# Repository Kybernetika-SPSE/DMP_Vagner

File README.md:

# Smart Hive

**Smart Hive** je projekt zaměřený na monitorování včelích úlů pomocí senzorů, které sbírají důležitá data o prostředí v úlech a jejich okolí. Data jsou přenášena přes I2C sběrnici do centrální (master) jednotky, která je dále odesílá do databáze. K těmto datům mohou uživatelé přistupovat online prostřednictvím webového rozhraní.

## Funkce
- **Sběr dat**: Senzory instalované ve včelích úlech monitorují teplotu, vlhkost, hmotnost úlu a hlukové znečištění.
- **Přenos dat**: Data z jednotlivých úlů jsou sbírána pomocí I2C komunikace a odesílána do centrální jednotky.
- **Uložení dat**: Centrální jednotka data ukládá do databáze.
- **Přístup k datům**: Uživatelé mohou přistupovat k datům online prostřednictvím webového rozhraní.

## Technické detaily
- **I2C komunikace**: Využívá se pro přenos dat mezi senzory v úlech a centrální jednotkou.
- **Databáze**: Data jsou ukládána do vzdálené databáze, která je přístupná uživatelům online.
- **Centrální jednotka**: Hlavní jednotka přijímá data od senzorů a zajišťuje jejich odesílání do databáze.
- **Webové rozhraní**: Poskytuje uživatelům přístup k živým datům a historickým záznamům.

## Požadavky
- **Hardware**: ESP32 s podporou I2C, senzory pro měření teploty, vlhkosti, hmotnosti a hluku, včelí úly.
- **Software**: Podpora I2C komunikace, databázový systém (např. MySQL, PostgreSQL), webový server pro přístup k datům.

## Použití
Po úspěšné instalaci systém začne shromažďovat a odesílat data ze senzorů v reálném čase. Uživatelé mohou k těmto datům přistupovat pomocí webového rozhraní, které umožňuje sledovat aktuální stav úlů a analyzovat historická data.

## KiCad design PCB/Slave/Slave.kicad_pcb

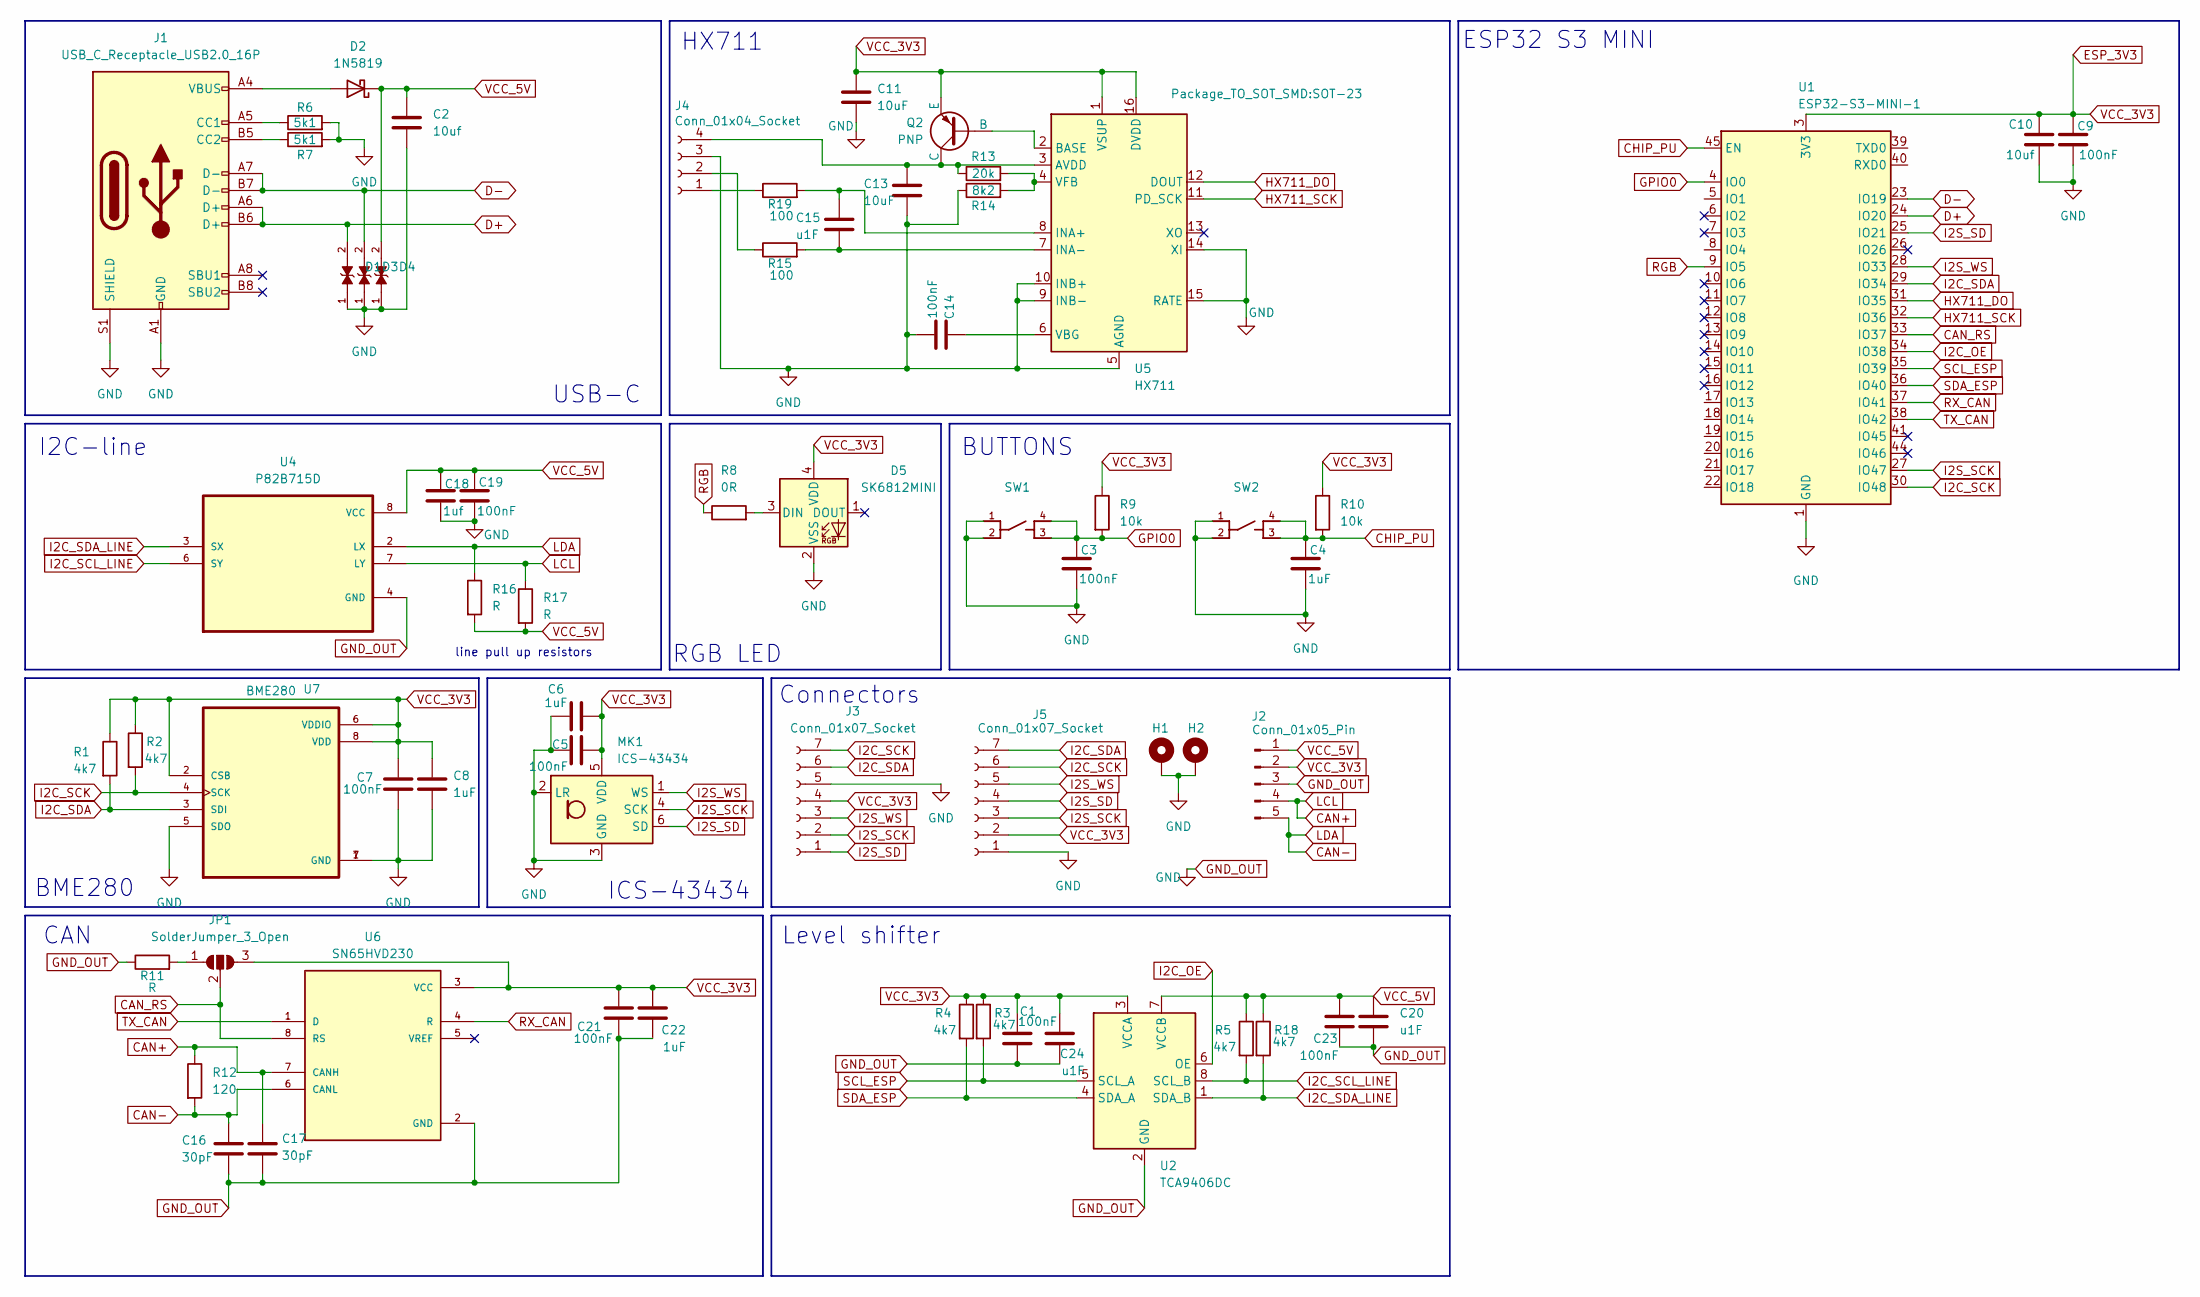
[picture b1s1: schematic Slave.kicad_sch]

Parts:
C1, C3, C5, C7, C9, C14, C19, C21, C23: 100nF; C_0603_1608Metric_Pad1.08x0.95mm_HandSolder
C2, C10: 10uf; C_0603_1608Metric_Pad1.08x0.95mm_HandSolder
C4, C6, C8, C22: 1uF; C_0603_1608Metric_Pad1.08x0.95mm_HandSolder
C11, C13: 10uF; C_0603_1608Metric_Pad1.08x0.95mm_HandSolder
C15, C20, C24: u1F; C_0603_1608Metric_Pad1.08x0.95mm_HandSolder
C16, C17: 30pF; C_0603_1608Metric_Pad1.08x0.95mm_HandSolder
C18: 1uf; C_0603_1608Metric_Pad1.08x0.95mm_HandSolder
D1, D3, D4: LESD5D5.0CT1G; TVS_LESD5D5.0CT1G; PARTREV O
D2: 1N5819; Nexperia_CFP3_SOD-123W
D5: SK6812MINI; LED_SK6812MINI_PLCC4_3.5x3.5mm_P1.75mm
H1, H2: MountingHole_Pad_MP; MountingHole_2.2mm_M2_Pad_Via
J1: USB_C_Receptacle_USB2.0_16P; USB_C_Receptacle_GCT_USB4105-xx-A_16P_TopMnt_Horizontal
J2: Conn_01x05_Pin; TerminalBlock_Phoenix_MPT-0,5-5-2.54_1x05_P2.54mm_Horizontal
J3: Conn_01x07_Socket; PinSocket_1x07_P2.54mm_Vertical
J4: Conn_01x04_Socket; PinHeader_1x04_P2.54mm_Vertical
J5: Conn_01x07_Socket; PinHeader_1x07_P1.00mm_Vertical_SMD_Pin1Left
JP1: SolderJumper_3_Open; SolderJumper-3_P1.3mm_Open_RoundedPad1.0x1.5mm
MK1: ICS-43434; InvenSense_ICS-43434-6_3.5x2.65mm
Q2: PNP; SOT-23
R1, R2, R3, R4, R5, R18: 4k7; R_0603_1608Metric_Pad0.98x0.95mm_HandSolder
R6, R7: 5k1; R_0603_1608Metric_Pad0.98x0.95mm_HandSolder
R8: 0R; R_0603_1608Metric_Pad0.98x0.95mm_HandSolder
R9, R10: 10k; R_0603_1608Metric_Pad0.98x0.95mm_HandSolder
R11, R16, R17: R; R_0603_1608Metric_Pad0.98x0.95mm_HandSolder
R12: 120; R_0603_1608Metric_Pad0.98x0.95mm_HandSolder
R13: 20k; R_0603_1608Metric_Pad0.98x0.95mm_HandSolder
R14: 8k2; R_0603_1608Metric_Pad0.98x0.95mm_HandSolder
R15, R19: 100; R_0603_1608Metric_Pad0.98x0.95mm_HandSolder
SW1, SW2: PTS810_SJM_250_SMTR_LFS; SW_PTS810_SJM_250_SMTR_LFS
U1: ESP32-S3-MINI-1; XCVR_ESP32-S3-MINI-1-N8
U2: TCA9406DC; SOP50P310X90-8N
U4: P82B715D; SOIC127P599X175-8N
U5: HX711; SOP-16_3.9x9.9mm_P1.27mm
U6: SN65HVD230; SOIC127P599X175-8N; PARTREV 02/2019
U7: BME280; PSON65P250X250X100-8N

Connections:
CAN+: C17.1, J2.4, R12.1, R17.1, U4.7 (LY), U6.7 (CANH)
CAN-: C16.1, J2.5, R12.2, R16.1, U4.2 (LX), U6.6 (CANL)
CAN_RS: JP1.2 (C), U1.33 (IO37), U6.8 (RS)
CHIP_PU: C4.1, R10.2, SW2.3, SW2.4, U1.45 (EN)
D+: D1.2, J1.A6 (D+), J1.B6 (D+), U1.24 (IO20)
D-: D3.2, J1.A7 (D-), J1.B7 (D-), U1.23 (IO19)
ESP_3V3: C1.2, C5.2, C6.2, C7.1, C8.1, C9.1, C10.1, C11.1, C21.1, C22.1, C24.1, D5.4 (VDD), J2.2, J3.4, J5.2, JP1.3 (B), MK1.5 (VDD), Q2.3 (E), R1.1, R2.1, R3.1, R4.1, R9.1, R10.1, U1.3 (3V3), U2.3 (VCCA), U5.1 (VSUP), U5.16 (DVDD), U6.3 (VCC), U7.2 (CSB), U7.6 (VDDIO), U7.8 (VDD)
GND_OUT: C1.1, C2.2, C3.2, C4.2, C5.1, C6.1, C7.2, C8.2, C9.2, C10.2, C11.2, C13.2, C14.2, C16.2, C17.2, C18.2, C19.2, C20.2, C21.2, C22.2, C23.1, C24.2, D1.1, D3.1, D4.1, D5.2 (VSS), H1.1, H2.1, J1.A1 (GND), J1.A12 (GND), J1.B1 (GND), J1.B12 (GND), J1.S1 (SHIELD), J2.3, J3.5, J4.3, J5.1, MK1.2 (LR), MK1.3 (GND), R6.2, R7.2, R11.1, R14.1, SW1.1, SW1.2, SW2.1, SW2.2, U1.1 (GND), U1.2 (GND), U1.42 (GND), U1.43 (GND), U1.46 (GND), U1.47 (GND), U1.48 (GND), U1.49 (GND), U1.50 (GND), U1.51 (GND), U1.52 (GND), U1.53 (GND), U1.54 (GND), U1.55 (GND), U1.56 (GND), U1.57 (GND), U1.58 (GND), U1.59 (GND), U1.60 (GND), U1.61 (GND), U1.62 (GND), U1.63 (GND), U1.64 (GND), U1.65 (GND), U2.2 (GND), U4.4 (GND), U5.5 (AGND), U5.9 (INB-), U5.10 (INB+), U5.14 (XI), U5.15 (RATE), U6.2 (GND), U7.1 (GND), U7.5 (SDO), U7.7 (GND)
GPIO0: C3.1, R9.2, SW1.3, SW1.4, U1.4 (IO0)
HX711_DO: U1.31 (IO35), U5.12 (DOUT)
HX711_SCK: U1.32 (IO36), U5.11 (PD_SCK)
I2C_OE: U1.34 (IO38), U2.6 (OE)
I2C_SCK: J3.7, J5.6, R2.2, U1.30 (IO48), U7.4 (SCK)
I2C_SCL_LINE: R5.2, U2.8 (SCL_B), U4.6 (SY)
I2C_SDA: J3.6, J5.7, R1.2, U1.29 (IO34), U7.3 (SDI)
I2C_SDA_LINE: R18.2, U2.1 (SDA_B), U4.3 (SX)
I2S_SCK: J3.2, J5.3, MK1.4 (SCK), U1.27 (IO47)
I2S_SD: J3.1, J5.4, MK1.6 (SD), U1.25 (IO21)
I2S_WS: J3.3, J5.5, MK1.1 (WS), U1.28 (IO33)
unnamed: D2.2 (A), J1.A4 (VBUS), J1.A9 (VBUS), J1.B4 (VBUS), J1.B9 (VBUS)
unnamed: D5.3 (DIN), R8.2
unnamed: J1.A5 (CC1), R6.1
unnamed: J1.B5 (CC2), R7.1
unnamed: J4.1, R19.1
unnamed: J4.2, R15.1
unnamed: C13.1, J4.4, Q2.1 (C), R13.1, U5.3 (AVDD)
unnamed: JP1.1 (A), R11.2
unnamed: Q2.2 (B), U5.2 (BASE)
unnamed: C15.1, R19.2, U5.8 (INA+)
unnamed: C15.2, R15.2, U5.7 (INA-)
unnamed: C14.1, U5.6 (VBG)
unnamed: R13.2, R14.2, U5.4 (VFB)
RGB: R8.1, U1.9 (IO5)
RX_CAN: U1.37 (IO41), U6.4 (R)
SCL_ESP: R3.2, U1.35 (IO39), U2.5 (SCL_A)
SDA_ESP: R4.2, U1.36 (IO40), U2.4 (SDA_A)
TX_CAN: U1.38 (IO42), U6.1 (D)
VCC_5V: C2.1, C18.1, C19.1, C20.1, C23.2, D2.1 (K), D4.2, J2.1, R5.1, R16.2, R17.2, R18.1, U2.7 (VCCB), U4.8 (VCC)

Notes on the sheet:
RGB LED
Connectors
BUTTONS
I2C-line
line pull up resistors
HX711
CAN
ICS-43434
Level shifter
BME280
ESP32 S3 MINI
USB-C

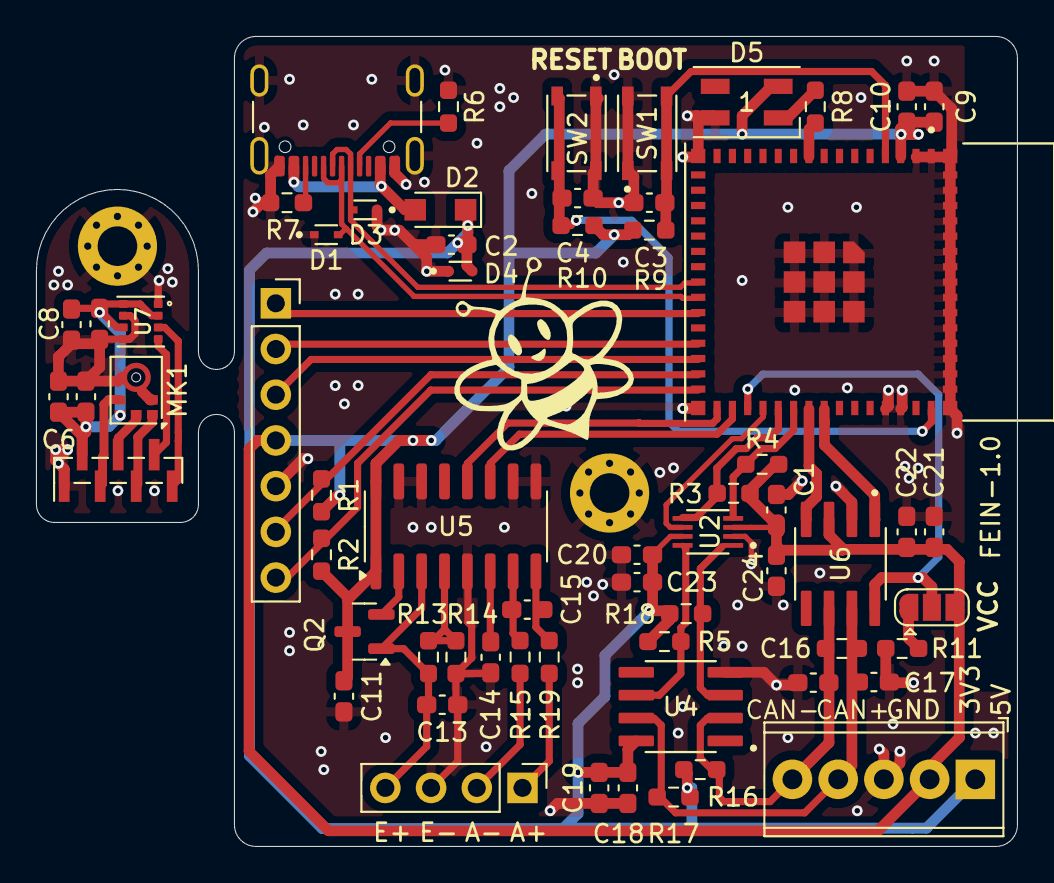
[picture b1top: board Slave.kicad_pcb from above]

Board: 2 copper layers, 54.5 x 45.0 mm, 65 parts (0 on the bottom side), 38 nets.

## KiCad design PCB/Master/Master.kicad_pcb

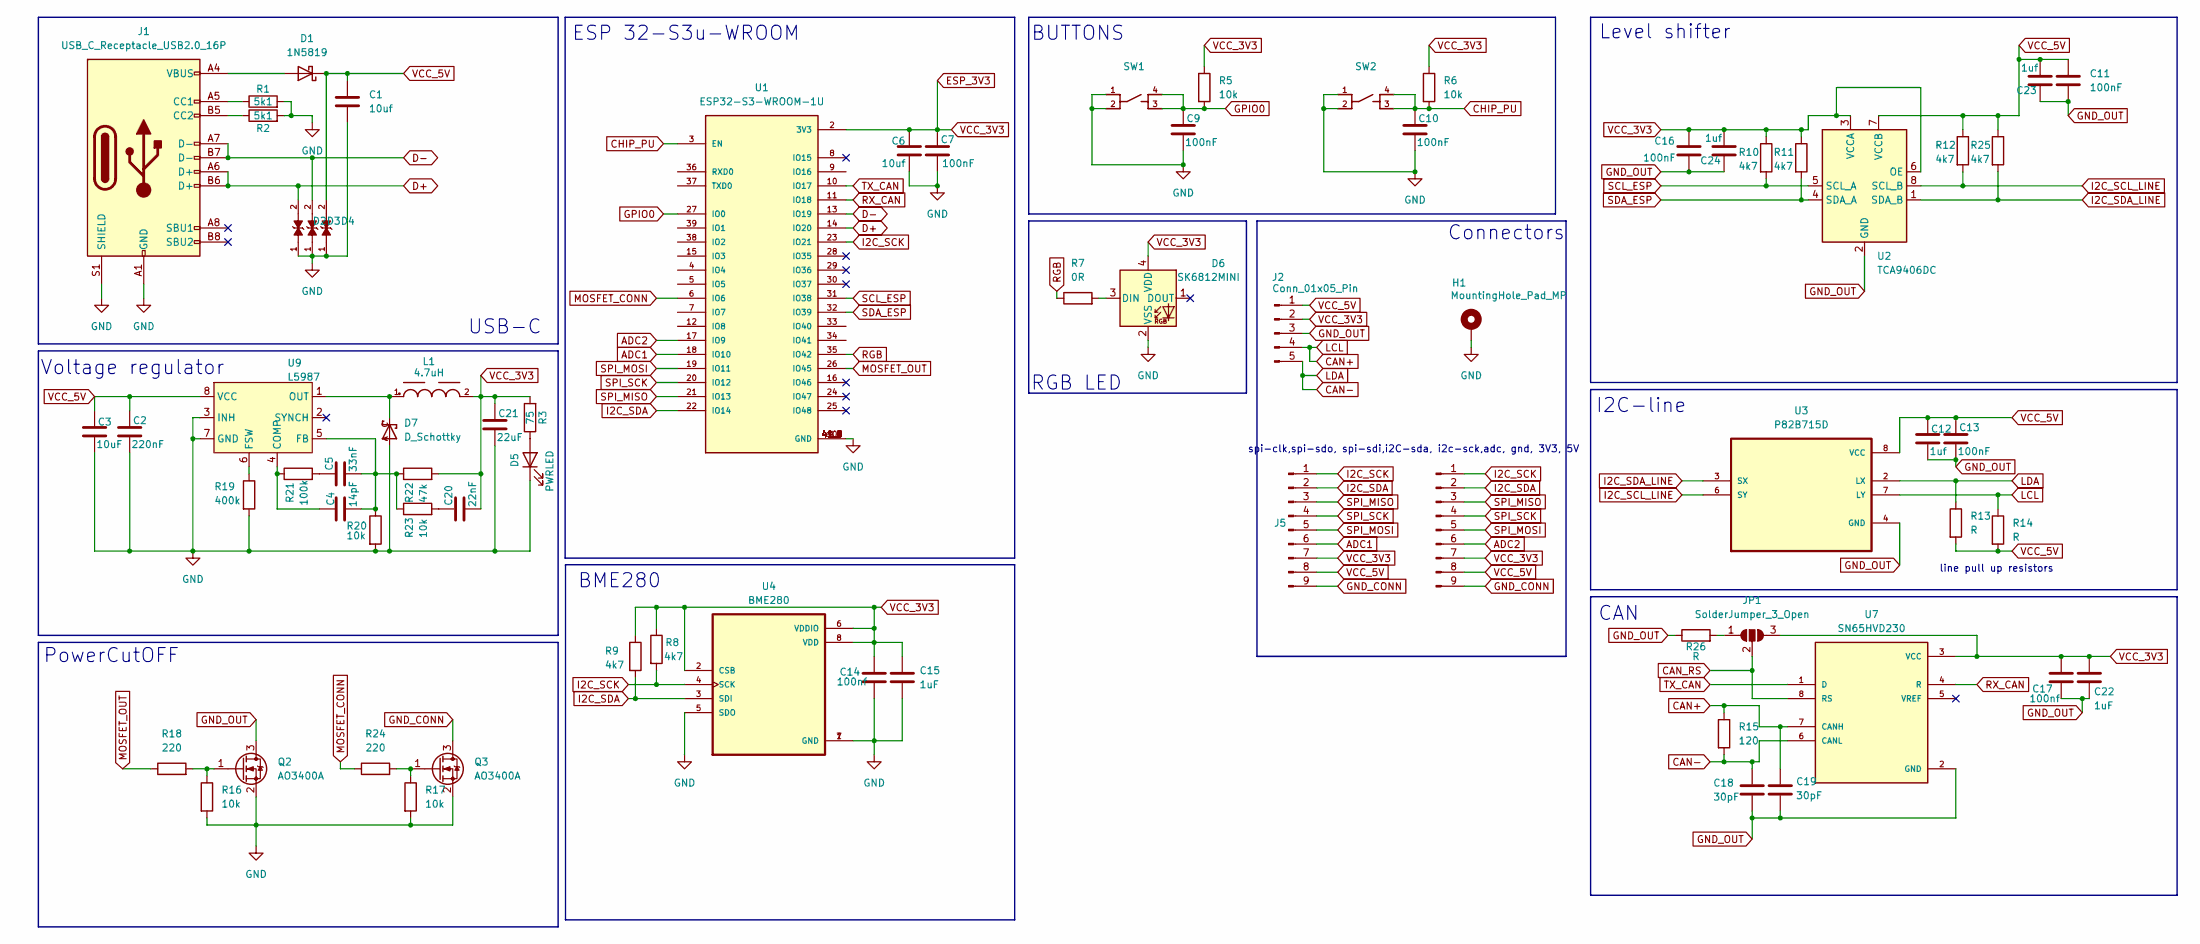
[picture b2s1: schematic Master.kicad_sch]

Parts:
C1, C6: 10uf; C_0603_1608Metric_Pad1.08x0.95mm_HandSolder
C2: 220nF; C_0603_1608Metric_Pad1.08x0.95mm_HandSolder
C3: 10uF; C_0603_1608Metric_Pad1.08x0.95mm_HandSolder
C4: 14pF; C_0603_1608Metric_Pad1.08x0.95mm_HandSolder
C5: 33nF; C_0603_1608Metric_Pad1.08x0.95mm_HandSolder
C7, C9, C10, C11, C13, C16: 100nF; C_0603_1608Metric_Pad1.08x0.95mm_HandSolder
C12, C23, C24: 1uf; C_0603_1608Metric_Pad1.08x0.95mm_HandSolder
C14, C17: 100nf; C_0603_1608Metric_Pad1.08x0.95mm_HandSolder
C15, C22: 1uF; C_0603_1608Metric_Pad1.08x0.95mm_HandSolder
C18, C19: 30pF; C_0603_1608Metric_Pad1.08x0.95mm_HandSolder
C20: 22nF; C_0603_1608Metric_Pad1.08x0.95mm_HandSolder
C21: 22uF; C_0603_1608Metric_Pad1.08x0.95mm_HandSolder
D1: 1N5819; Nexperia_CFP3_SOD-123W
D2, D3, D4: LESD5D5.0CT1G; TVS_LESD5D5.0CT1G; PARTREV O
D5: PWRLED; LED_0603_1608Metric_Pad1.05x0.95mm_HandSolder
D6: SK6812MINI; LED_SK6812MINI_PLCC4_3.5x3.5mm_P1.75mm
D7: D_Schottky; SOD-123
H1: MountingHole_Pad_MP; MountingHole_2.2mm_M2_Pad_Via
J1: USB_C_Receptacle_USB2.0_16P; USB_C_Receptacle_GCT_USB4105-xx-A_16P_TopMnt_Horizontal
J2: Conn_01x05_Pin; TerminalBlock_Phoenix_MPT-0,5-5-2.54_1x05_P2.54mm_Horizontal
J5, J6: Conn_01x09_Pin; PinHeader_1x09_P2.54mm_Vertical
JP1: SolderJumper_3_Open; SolderJumper-3_P1.3mm_Open_RoundedPad1.0x1.5mm
L1: 4.7uH; WE-PD2_5848; DigiKey_Part_Number 732-1272-2-ND
Q2, Q3: AO3400A; SOT-23
R1, R2: 5k1; R_0603_1608Metric_Pad0.98x0.95mm_HandSolder
R3: 75; R_0603_1608Metric_Pad0.98x0.95mm_HandSolder
R5, R6, R16, R17, R20, R23: 10k; R_0603_1608Metric_Pad0.98x0.95mm_HandSolder
R7: 0R; R_0603_1608Metric_Pad0.98x0.95mm_HandSolder
R8, R9, R10, R11, R12, R25: 4k7; R_0603_1608Metric_Pad0.98x0.95mm_HandSolder
R13, R14, R26: R; R_0603_1608Metric_Pad0.98x0.95mm_HandSolder
R15: 120; R_0603_1608Metric_Pad0.98x0.95mm_HandSolder
R18, R24: 220; R_0603_1608Metric_Pad0.98x0.95mm_HandSolder
R19: 400k; R_0805_2012Metric_Pad1.20x1.40mm_HandSolder
R21: 100k; R_0805_2012Metric_Pad1.20x1.40mm_HandSolder
R22: 47k; R_0603_1608Metric_Pad0.98x0.95mm_HandSolder
SW1, SW2: PTS810_SJM_250_SMTR_LFS; SW_PTS810_SJM_250_SMTR_LFS
U1: ESP32-S3-WROOM-1U; XCVR_ESP32-S3-WROOM-1U; PARTREV v0.6
U2: TCA9406DC; SOP50P310X90-8N
U3: P82B715D; SOIC127P599X175-8N
U4: BME280; PSON65P250X250X100-8N
U7: SN65HVD230; SOIC127P599X175-8N; PARTREV 02/2019
U9: L5987; SOIC127P600X170-9N

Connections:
ADC1: J5.6, U1.18 (IO10)
ADC2: J6.6, U1.17 (IO9)
CAN+: C19.1, J2.4, R14.1, R15.1, U3.7 (LY), U7.7 (CANH)
CAN-: C18.1, J2.5, R13.1, R15.2, U3.2 (LX), U7.6 (CANL)
CAN_RS: JP1.2 (C), U7.8 (RS)
CHIP_PU: C10.1, R6.2, SW2.3, SW2.4, U1.3 (EN)
D+: D2.2, J1.A6 (D+), J1.B6 (D+), U1.14 (IO20)
D-: D3.2, J1.A7 (D-), J1.B7 (D-), U1.13 (IO19)
ESP_3V3: C6.1, C7.1, C14.1, C15.1, C16.2, C17.1, C20.2, C21.1, C22.1, C24.2, D6.4 (VDD), J2.2, J5.7, J6.7, JP1.3 (B), L1.2, R3.2, R5.1, R6.1, R8.1, R9.1, R10.1, R11.1, R22.2, U1.2 (3V3), U2.3 (VCCA), U2.6 (OE), U4.2 (CSB), U4.6 (VDDIO), U4.8 (VDD), U7.3 (VCC)
GND: C1.2, C2.2, C3.2, C6.2, C7.2, C9.2, C10.2, C14.2, C15.2, C21.2, D2.1, D3.1, D4.1, D5.1 (K), D6.2 (VSS), D7.A, H1.1, J1.A1 (GND), J1.A12 (GND), J1.B1 (GND), J1.B12 (GND), J1.S1 (SHIELD), Q2.2 (S), Q3.2 (S), R1.2, R2.2, R16.2, R17.2, R19.2, R20.2, SW1.1, SW1.2, SW2.1, SW2.2, U1.1 (GND), U1.40 (GND), U1.41_1 (GND), U1.41_2 (GND), U1.41_3 (GND), U1.41_4 (GND), U1.41_5 (GND), U1.41_6 (GND), U1.41_7 (GND), U1.41_8 (GND), U1.41_9 (GND), U4.1 (GND), U4.5 (SDO), U4.7 (GND), U9.3 (INH), U9.7 (GND)
GND_CONN: J5.9, J6.9, Q3.3 (D)
GND_OUT: C11.2, C12.2, C13.2, C16.1, C17.2, C18.2, C19.2, C22.2, C23.1, C24.1, J2.3, Q2.3 (D), R26.1, U2.2 (GND), U3.4 (GND), U7.2 (GND)
GPIO0: C9.1, R5.2, SW1.3, SW1.4, U1.27 (IO0)
I2C_SCK: J5.1, J6.1, R8.2, U1.23 (IO21), U4.4 (SCK)
I2C_SCL_LINE: R12.2, U2.8 (SCL_B), U3.6 (SY)
I2C_SDA: J5.2, J6.2, R9.2, U1.22 (IO14), U4.3 (SDI)
I2C_SDA_LINE: R25.2, U2.1 (SDA_B), U3.3 (SX)
MOSFET_CONN: R24.1, U1.6 (IO6)
MOSFET_OUT: R18.1, U1.26 (IO45)
unnamed: C5.1, R21.2
unnamed: C20.1, R23.2
unnamed: D1.2 (A), J1.A4 (VBUS), J1.A9 (VBUS), J1.B4 (VBUS), J1.B9 (VBUS)
unnamed: D5.2 (A), R3.1
unnamed: D6.3 (DIN), R7.2
unnamed: J1.A5 (CC1), R1.1
unnamed: J1.B5 (CC2), R2.1
unnamed: JP1.1 (A), R26.2
unnamed: Q2.1 (G), R16.1, R18.2
unnamed: Q3.1 (G), R17.1, R24.2
unnamed: C4.1, R21.1, U9.4 (COMP)
unnamed: C4.2, C5.2, R20.1, R22.1, R23.1, U9.5 (FB)
unnamed: R19.1, U9.6 (FSW)
unnamed: D7.C, L1.1, U9.1 (OUT)
RGB: R7.1, U1.35 (IO42)
RX_CAN: U1.11 (IO18), U7.4 (R)
SCL_ESP: R10.2, U1.31 (IO38), U2.5 (SCL_A)
SDA_ESP: R11.2, U1.32 (IO39), U2.4 (SDA_A)
SPI_MISO: J5.3, J6.3, U1.21 (IO13)
SPI_MOSI: J5.5, J6.5, U1.19 (IO11)
SPI_SCK: J5.4, J6.4, U1.20 (IO12)
TX_CAN: U1.10 (IO17), U7.1 (D)
VCC_5V: C1.1, C2.1, C3.1, C11.1, C12.1, C13.1, C23.2, D1.1 (K), D4.2, J2.1, J5.8, J6.8, R12.1, R13.2, R14.2, R25.1, U2.7 (VCCB), U3.8 (VCC), U9.8 (VCC)

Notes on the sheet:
Connectors
Level shifter
CAN
BME280
line pull up resistors
Voltage regulator
USB-C
spi-clk,spi-sdo, spi-sdi,i2C-sda, i2c-sck,adc, gnd, 3V3, 5V
RGB LED
PowerCutOFF
ESP 32-S3u-WROOM
BUTTONS
I2C-line

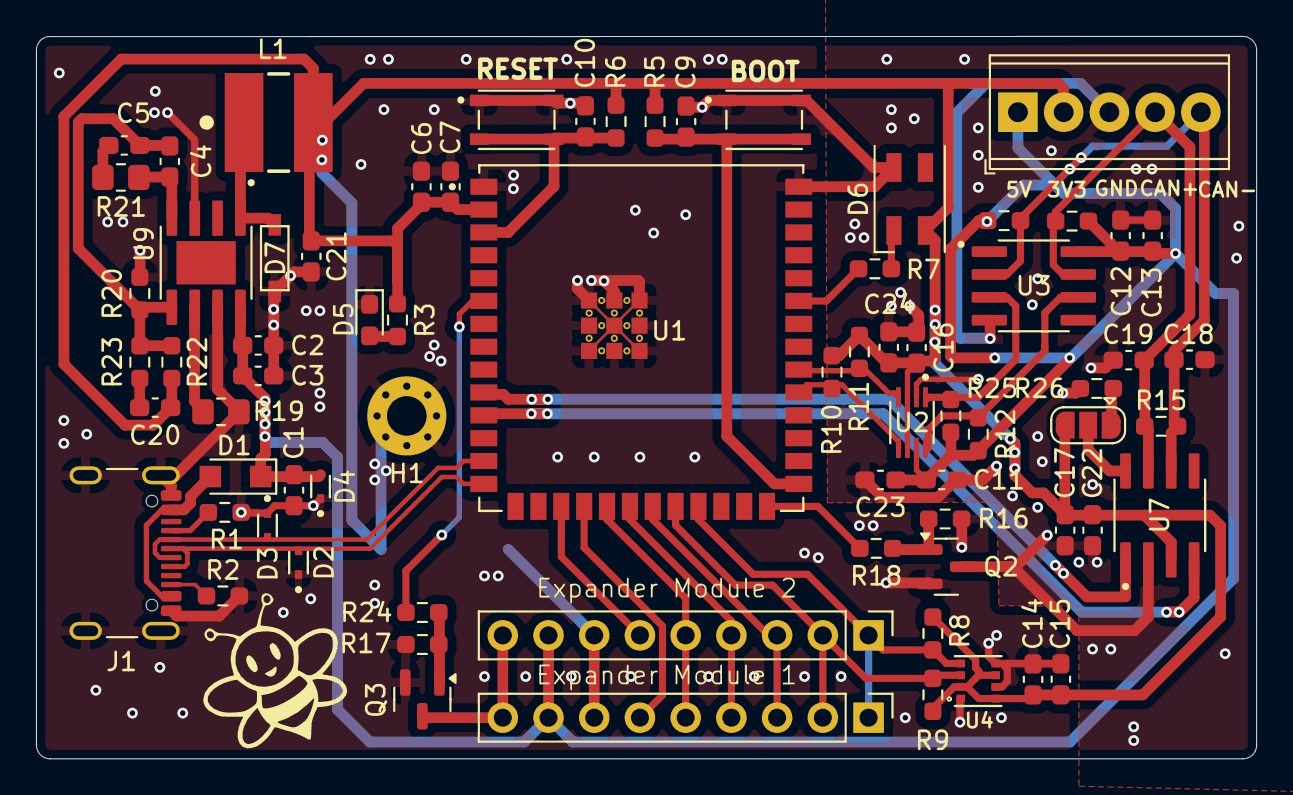
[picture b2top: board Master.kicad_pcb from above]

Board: 2 copper layers, 67.8 x 40.1 mm, 72 parts (0 on the bottom side), 42 nets.

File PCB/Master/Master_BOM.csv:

Reference,Value,Datasheet,Footprint,Qty,DNP
"C1,C6",10uf,~,Capacitor_SMD:C_0603_1608Metric_Pad1.08x0.95mm_HandSolder,2,
C2,220nF,~,Capacitor_SMD:C_0603_1608Metric_Pad1.08x0.95mm_HandSolder,1,
C3,10uF,~,Capacitor_SMD:C_0603_1608Metric_Pad1.08x0.95mm_HandSolder,1,
C4,14pF,~,Capacitor_SMD:C_0603_1608Metric_Pad1.08x0.95mm_HandSolder,1,
C5,33nF,~,Capacitor_SMD:C_0603_1608Metric_Pad1.08x0.95mm_HandSolder,1,
"C7,C9,C10,C13,C14",0u1F,~,Capacitor_SMD:C_0603_1608Metric_Pad1.08x0.95mm_HandSolder,5,
"C8,C12",1uf,~,Capacitor_SMD:C_0603_1608Metric_Pad1.08x0.95mm_HandSolder,2,
C11,100pF,~,Capacitor_SMD:C_0603_1608Metric_Pad1.08x0.95mm_HandSolder,1,
C15,1uF,~,Capacitor_SMD:C_0603_1608Metric_Pad1.08x0.95mm_HandSolder,1,
"C18,C19",30pF,~,Capacitor_SMD:C_0603_1608Metric_Pad1.08x0.95mm_HandSolder,2,
C20,22nF,~,Capacitor_SMD:C_0603_1608Metric_Pad1.08x0.95mm_HandSolder,1,
C21,22uF,~,Capacitor_SMD:C_0603_1608Metric_Pad1.08x0.95mm_HandSolder,1,
D1,1N5819,http://www.vishay.com/docs/88525/1n5817.pdf,Diode_SMD:Nexperia_CFP3_SOD-123W,1,
"D2,D3,D4",LESD5D5.0CT1G,,LESD5D5.0CT1G:TVS_LESD5D5.0CT1G,3,
D5,PWRLED,~,LED_SMD:LED_0603_1608Metric_Pad1.05x0.95mm_HandSolder,1,
D6,SK6812MINI,https://cdn-shop.adafruit.com/product-files/2686/SK6812MINI_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,LED_SMD:LED_SK6812MINI_PLCC4_3.5x3.5mm_P1.75mm,1,
D7,D_Schottky,~,PMEG2010AEH:SOD-123,1,
J1,USB_C_Receptacle_USB2.0_16P,https://www.usb.org/sites/default/files/documents/usb_type-c.zip,Connector_USB:USB_C_Receptacle_GCT_USB4105-xx-A_16P_TopMnt_Horizontal,1,
J2,Conn_01x05_Pin,~,"TerminalBlock_Phoenix:TerminalBlock_Phoenix_MPT-0,5-5-2.54_1x05_P2.54mm_Horizontal",1,
"J5,J6",Conn_01x09_Pin,~,Connector_PinHeader_2.54mm:PinHeader_1x09_P2.54mm_Vertical,2,
L1,4.7uH,~,WE-PD2_5848:WE-PD2_5848,1,
"Q2,Q3",AO3400A,http://www.aosmd.com/pdfs/datasheet/AO3400A.pdf,Package_TO_SOT_SMD:SOT-23,2,
"R1,R2",5k1,~,Resistor_SMD:R_0603_1608Metric_Pad0.98x0.95mm_HandSolder,2,
R3,75,~,Resistor_SMD:R_0603_1608Metric_Pad0.98x0.95mm_HandSolder,1,
"R4,R5,R6,R16,R17,R20,R23",10k,~,Resistor_SMD:R_0603_1608Metric_Pad0.98x0.95mm_HandSolder,7,
R7,0R,~,Resistor_SMD:R_0603_1608Metric_Pad0.98x0.95mm_HandSolder,1,
"R8,R9,R11,R12",4k7,~,Resistor_SMD:R_0603_1608Metric_Pad0.98x0.95mm_HandSolder,4,
R10,200k,~,Resistor_SMD:R_0603_1608Metric_Pad0.98x0.95mm_HandSolder,1,
"R13,R14",R,~,Resistor_SMD:R_0603_1608Metric_Pad0.98x0.95mm_HandSolder,2,
R15,120,~,Resistor_SMD:R_0603_1608Metric_Pad0.98x0.95mm_HandSolder,1,
"R18,R24",220,~,Resistor_SMD:R_0603_1608Metric_Pad0.98x0.95mm_HandSolder,2,
R19,400k,~,Resistor_SMD:R_0603_1608Metric_Pad0.98x0.95mm_HandSolder,1,
R21,100k,~,Resistor_SMD:R_0603_1608Metric_Pad0.98x0.95mm_HandSolder,1,
R22,45k,~,Resistor_SMD:R_0603_1608Metric_Pad0.98x0.95mm_HandSolder,1,
"SW1,SW2",PTS810_SJM_250_SMTR_LFS,,PTS810_SJM_250_SMTR_LFS:SW_PTS810_SJM_250_SMTR_LFS,2,
U1,ESP32-S3-WROOM-1U,,ESP32-S3-WROOM-1U:XCVR_ESP32-S3-WROOM-1U,1,
U3,P82B715D,,P82B715D:SOIC127P599X175-8N,1,
U4,PCA9306DCURE4,,PCA9306DCURE4:SOP50P310X90-8N,1,
U5,BMP280,,BMP280:XDCR_BMP280,1,
U7,SN65HVD230,,SN65HVD230:SOIC127P599X175-8N,1,
U9,L5987,,L5987A:SOIC127P600X170-9N,1,

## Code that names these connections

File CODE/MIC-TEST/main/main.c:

#include <stdio.h>
#include <inttypes.h> // For PRIu32
#include "freertos/FreeRTOS.h"
#include "freertos/task.h"
#include "driver/i2s.h"
#include "esp_log.h"

// Constants
#define I2S_NUM         I2S_NUM_0
#define I2S_SCK_PIN     37  // I²S Clock Pin
#define I2S_WS_PIN      38  // I²S Word Select Pin
#define I2S_SD_PIN      39  // I²S Data Pin
#define SAMPLE_RATE     16000
#define FFT_SIZE        256

// Logging tag
static const char *TAG = "BeeHiveMonitor";

// Function Prototypes
void i2s_audio_init();
void simple_task(void *arg);

/* I2S Initialization */
void i2s_audio_init() {
    i2s_config_t i2s_config = {
        .mode = I2S_MODE_MASTER | I2S_MODE_RX,
        .sample_rate = SAMPLE_RATE,
        .bits_per_sample = I2S_BITS_PER_SAMPLE_16BIT,
        .channel_format = I2S_CHANNEL_FMT_ONLY_LEFT,
        .communication_format = I2S_COMM_FORMAT_I2S_MSB,
        .intr_alloc_flags = ESP_INTR_FLAG_LEVEL1,
        .dma_buf_count = 4,
        .dma_buf_len = FFT_SIZE,
        .use_apll = false,
        .tx_desc_auto_clear = false,
        .fixed_mclk = 0
    };

    i2s_pin_config_t pin_config = {
        .bck_io_num = I2S_SCK_PIN,
        .ws_io_num = I2S_WS_PIN,
        .data_out_num = I2S_PIN_NO_CHANGE,
        .data_in_num = I2S_SD_PIN,
    };

    ESP_ERROR_CHECK(i2s_driver_install(I2S_NUM, &i2s_config, 0, NULL));
    ESP_ERROR_CHECK(i2s_set_pin(I2S_NUM, &pin_config));
    ESP_LOGI(TAG, "I²S audio initialized.");
}

/* Simple Task for Testing */
void simple_task(void *arg) {
    while (1) {
        ESP_LOGI(TAG, "Simple task is running. Free heap: %lu bytes", (unsigned long)esp_get_free_heap_size());
        vTaskDelay(pdMS_TO_TICKS(5000));
    }
}

/* Main Function */
void app_main(void) {
    ESP_LOGI(TAG, "Initializing Bee Hive Monitor...");

    // Initialize I2S for audio
    i2s_audio_init();

    // Log free heap memory
    ESP_LOGI(TAG, "Free heap before tasks: %lu bytes", (unsigned long)esp_get_free_heap_size());

    // Start simple task
    if (xTaskCreate(simple_task, "simple_task", 4096, NULL, 10, NULL) != pdPASS) {
        ESP_LOGE(TAG, "Failed to create simple_task");
    } else {
        ESP_LOGI(TAG, "simple_task created successfully.");
    }

    // Keep the main function alive
    while (1) {
        ESP_LOGI(TAG, "Bee Hive Monitor is running. Free heap: %lu bytes", (unsigned long)esp_get_free_heap_size());
        vTaskDelay(pdMS_TO_TICKS(5000));
    }
}

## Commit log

2024-09-23 Rename DMP_zadani_VAGNER.docx to Zadani/DMP_zadani_VAGNER.docx
2024-09-23 Rename DMP_zadani_VAGNER.pdf to Zadani/DMP_zadani_VAGNER.pdf
2024-09-26 Rename Smart Hive.md to README.md
2024-09-26 KICAD COMMIT
2024-09-29 PCB-Update
2024-09-30 text
2024-09-30 txt_change
2024-10-03 added schematic
2024-10-10 Small changes to the pcb(Master and Slave))
2024-10-13 Added CAP
2024-10-14 From 0603 TO 0805 at power supply
2024-10-15 Changed bmp for bme
2024-10-15 Added I2C PullUp Resistors
2024-10-17 repaired HX711
2024-10-21 update both
2024-10-31 added Update for October
2025-01-07 Update_Prosinec
2025-01-13 CODE FOLDER
2025-02-06 Update LICENSE
2025-02-06 all code
2025-04-10 SETUP FOR HANDOVER1
2025-04-10 Handover setup 2
